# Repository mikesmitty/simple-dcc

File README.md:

# simple-dcc

A simple LCC-connected DCC command station, because sometimes a tool just needs to do the one thing.

## Features

- DCC signal generation
- RailCom cutout support
- CV writes on the main, including a long address in one step (CV17 and CV18) and advanced consists (CV19)
- CV reads on the main over RailCom, with the detector shield in `hardware/railcom-detector`
- DCC accessory decoders (turnouts and signal aspects) through the well-known LCC accessory events

## Current Reference Hardware

- **Board:** Adafruit Metro RP2350 (RP2350B, 16 MB flash)
- **Motor Shield:** EX-MotorShield8874
- **Protocol:** LCC/OpenLCB via GridConnect CAN frames over USB CDC

## Prerequisites

- [Pico SDK](https://github.com/raspberrypi/pico-sdk) (2.x)
- [FreeRTOS Kernel](https://github.com/FreeRTOS/FreeRTOS-Kernel) with RP2350 community port
- ARM GCC toolchain with newlib (e.g., [ARM GNU Toolchain](https://developer.arm.com/Tools%20and%20Software/GNU%20Toolchain))
- CMake 3.13+
- [picotool](https://github.com/raspberrypi/picotool) (for UF2 generation)

### macOS (Homebrew)

```bash
brew install cmake
brew install --cask gcc-arm-embedded
brew install picotool
```

### Clone dependencies

```bash
# Pico SDK
git clone https://github.com/raspberrypi/pico-sdk.git
cd pico-sdk && git submodule update --init && cd ..

# FreeRTOS Kernel (with RP2350 community port)
git clone https://github.com/FreeRTOS/FreeRTOS-Kernel.git
cd FreeRTOS-Kernel && git submodule update --init && cd ..
```

## Build

Set environment variables pointing to the SDK and FreeRTOS Kernel:

```bash
export PICO_SDK_PATH=/path/to/pico-sdk
export FREERTOS_KERNEL_PATH=/path/to/FreeRTOS-Kernel
```

If the ARM toolchain is not on your PATH, also set:

```bash
export PICO_TOOLCHAIN_PATH=/path/to/arm-none-eabi/bin
```

Then build:

```bash
mkdir build && cd build
cmake ..
make -j$(nproc)
```

Output: `build/simple-dcc.uf2`

## Flash

1. Hold BOOT on the Metro and connect USB
2. Drag `simple-dcc.uf2` to the mounted `RP2350` drive

Or use picotool:

```bash
picotool load build/simple-dcc.uf2
picotool reboot
```

## Host-side Tests

Unit tests run on the host (no hardware required):

```bash
cd test
mkdir -p build && cd build
cmake .. && make && ctest
```

## License

MIT

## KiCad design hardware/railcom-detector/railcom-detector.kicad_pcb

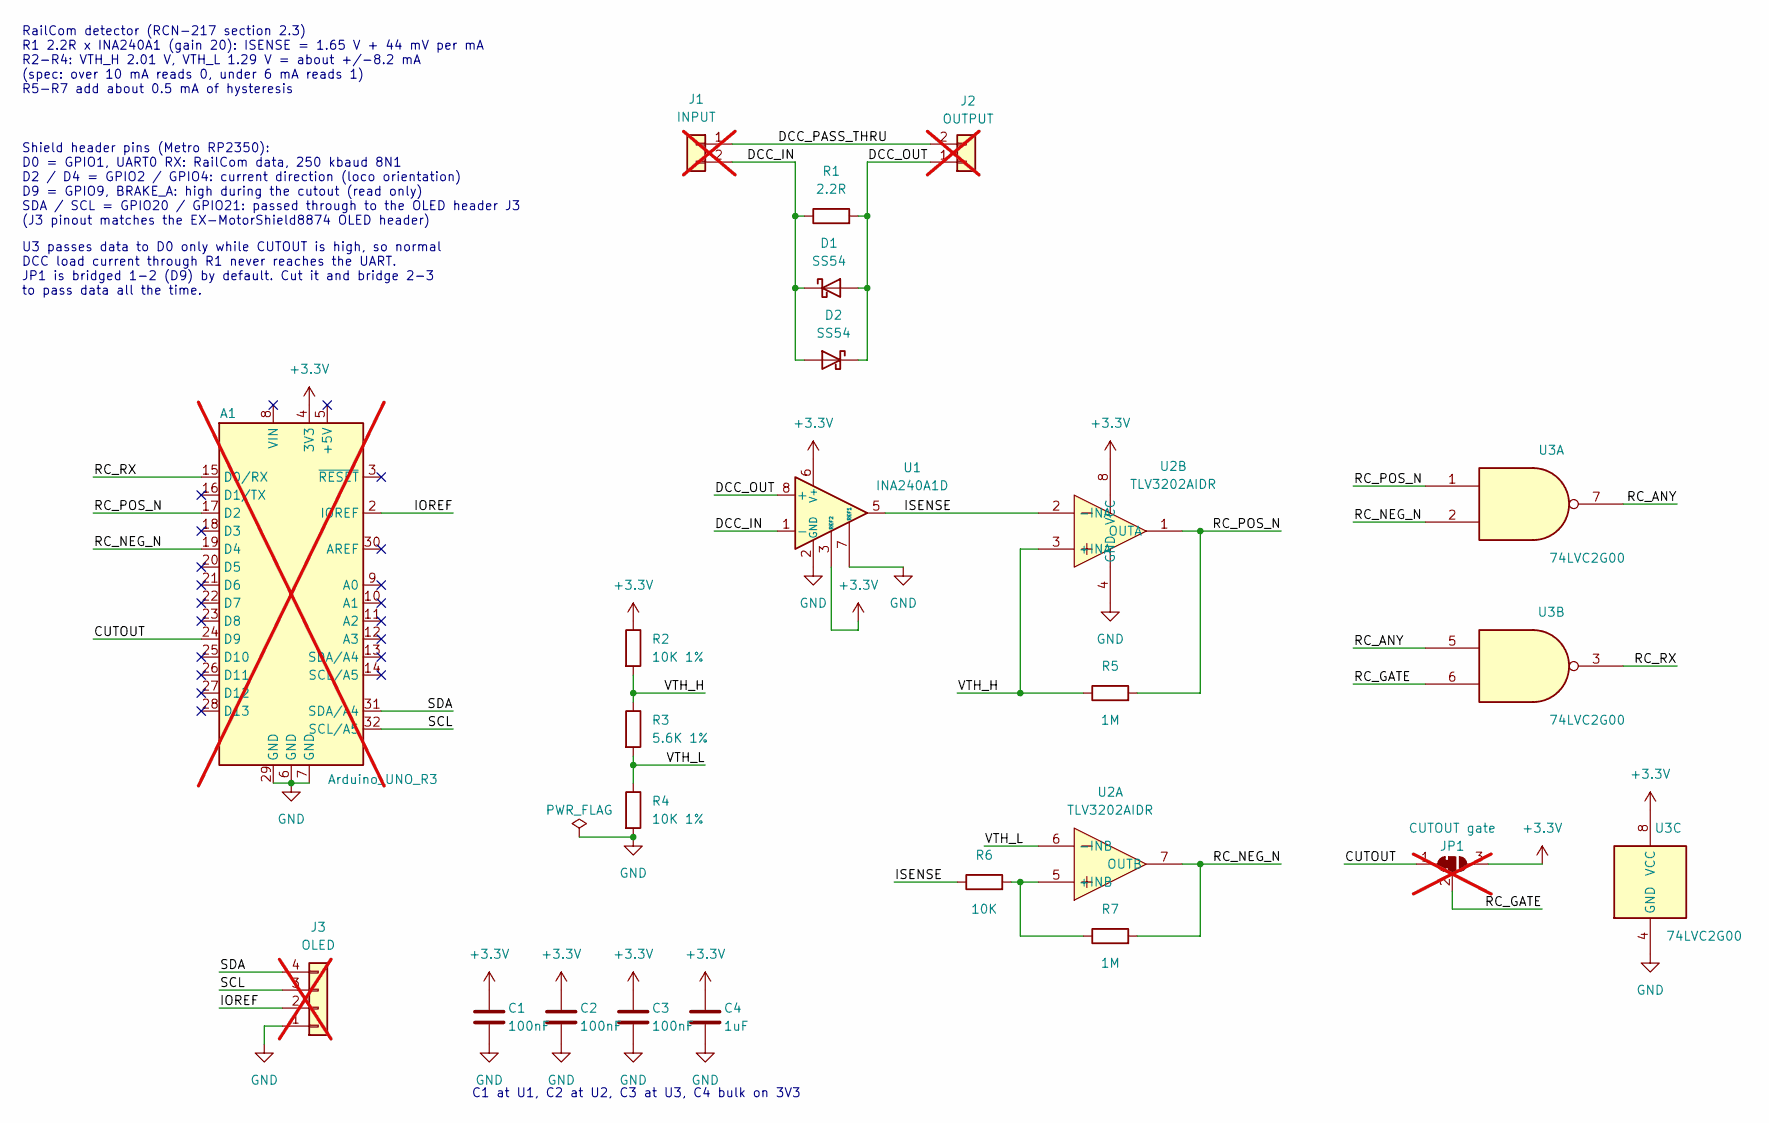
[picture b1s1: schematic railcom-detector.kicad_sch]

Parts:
A1: Arduino_UNO_R3; Arduino_UNO_R3_Shield; not fitted
C1, C2, C3: 100nF; C_0603_1608Metric; LCSC C14663
C4: 1uF; C_0603_1608Metric; LCSC C15849
D1, D2: SS54; D_SMA; LCSC C22452
J1: INPUT; PhoenixContact_MC_1,5_2-G-3.5_1x02_P3.50mm_Horizontal; LCSC C409115; not fitted
J2: OUTPUT; PhoenixContact_MC_1,5_2-G-3.5_1x02_P3.50mm_Horizontal; LCSC C409115; not fitted
J3: OLED; PinSocket_1x04_P2.54mm_Vertical; LCSC C2685089; not fitted
JP1: CUTOUT gate; SolderJumper-3_P1.3mm_Bridged12_RoundedPad1.0x1.5mm_NumberL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; not fitted
R1: 2.2R; R_2512_6332Metric; LCSC C2907574
R2, R4: 10K 1%; R_0603_1608Metric; LCSC C25804
R3: 5.6K 1%; R_0603_1608Metric; LCSC C23189
R5, R7: 1M; R_0603_1608Metric; LCSC C22935
R6: 10K; R_0603_1608Metric; LCSC C25804
U1: INA240A1D; SOIC-8_3.9x4.9mm_P1.27mm; LCSC C2060769
U2: TLV3202AIDR; SOIC-8_L4.9-W3.9-P1.27-LS6.0-BL; MPN TLV3202AIDR; LCSC Part C129325
U3: 74LVC2G00; SSOP-8_2.95x2.8mm_P0.65mm; MPN SN74LVC2G00DCTR; LCSC C2682112

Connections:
+3.3V: A1.4 (3V3), C1.1, C2.1, C3.1, C4.1, JP1.3 (B), R2.1, U1.3 (REF2), U1.6 (V+), U2.8 (VCC), U3.8 (VCC)
/CUTOUT: A1.24 (D9), JP1.1 (A)
/DCC_IN: D1.1 (K), D2.2 (A), J1.2, R1.1, U1.1 (-)
/DCC_OUT: D1.2 (A), D2.1 (K), J2.1, R1.2, U1.8 (+)
/DCC_PASS_THRU: J1.1, J2.2
/IOREF: A1.2 (IOREF), J3.2
/ISENSE: R6.1, U1.5, U2.2 (-INA)
/RC_ANY: U3.5, U3.7
/RC_GATE: JP1.2 (C), U3.6
/RC_NEG_N: A1.19 (D4), R7.2, U2.7 (OUTB), U3.2
/RC_POS_N: A1.17 (D2), R5.2, U2.1 (OUTA), U3.1
/RC_RX: A1.15 (D0/RX), U3.3
/SCL: A1.32 (SCL/A5), J3.3
/SDA: A1.31 (SDA/A4), J3.4
/VTH_H: R2.2, R3.1, R5.1, U2.3 (+INA)
/VTH_L: R3.2, R4.1, U2.6 (-INB)
GND: A1.6 (GND), A1.7 (GND), A1.29 (GND), C1.2, C2.2, C3.2, C4.2, J3.1, R4.2, U1.2 (GND), U1.4 (GND), U1.7 (REF1), U2.4 (GND), U3.4 (GND)
unnamed: R6.2, R7.1, U2.5 (+INB)

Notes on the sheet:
U3 passes data to D0 only while CUTOUT is high, so normal DCC load current through R1 never reaches the UART. JP1 is bridged 1-2 (D9) by default. Cut it and bridge 2-3 to pass data all the time.
C1 at U1, C2 at U2, C3 at U3, C4 bulk on 3V3
Shield header pins (Metro RP2350): D0 = GPIO1, UART0 RX: RailCom data, 250 kbaud 8N1 D2 / D4 = GPIO2 / GPIO4: current direction (loco orientation) D9 = GPIO9, BRAKE_A: high during the cutout (read only) SDA / SCL = GPIO20 / GPIO21: passed through to the OLED header J3 (J3 pinout matches the EX-Moto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
RailCom detector (RCN-217 section 2.3) R1 2.2R x INA240A1 (gain 20): ISENSE = 1.65 V + 44 mV per mA R2-R4: VTH_H 2.01 V, VTH_L 1.29 V = about +/-8.2 mA (spec: over 10 mA reads 0, under 6 mA reads 1) R5-R7 add about 0.5 mA of hysteresis

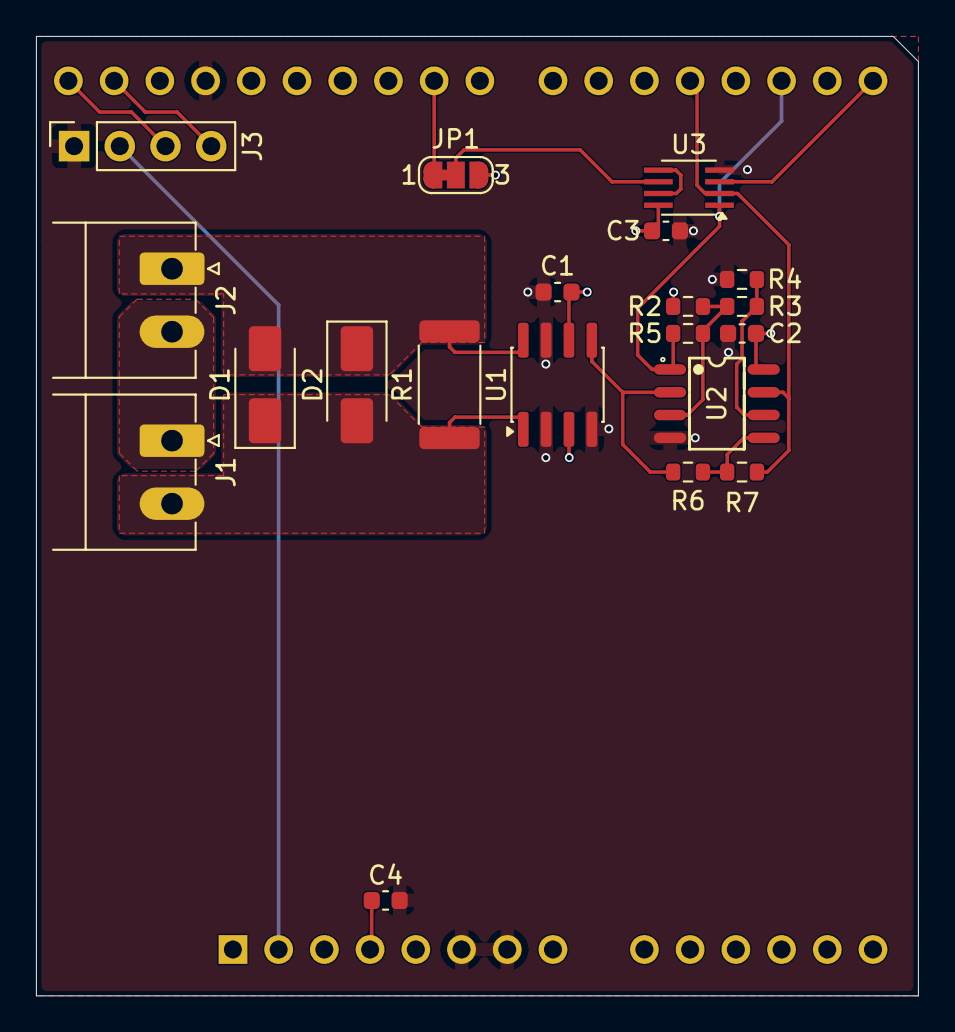
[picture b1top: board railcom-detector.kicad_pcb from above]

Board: 4 copper layers, 49.0 x 53.3 mm, 21 parts (1 on the bottom side), 18 nets.

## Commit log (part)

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2026-03-27 docs: clean up initial README
2026-03-27 chore: remove .vscode from .gitignore
2026-03-28 chore: add Makefile for ease of building
2026-03-28 feat(lcc): add CDI and RAM-backed config memory
    - Add src/cdi.xml with initial node identification and traction settings.
    - Generate src/cdi_data.c/h with pretty-printed XML (1204 bytes).
    - Fix 'premature end of file' in JMRI by excluding null terminator from reported CDI space.
    - Fix 'element type cdi must be followed by attribute' by ensuring root attributes are space-separated.
    - Implement RAM-backed config memory (space 0xFD) for CS settings like auto-claim.
    - Support auto-claim DCC address enable/disable toggle via LCC configuration.
2026-03-28 fix(lcc): save config to flash without stack overflow
    - Use heap allocation in nv_storage_write to prevent timer task stack overflow
    - Align cs_config_mem to 256 bytes for flash programming
    - Reset node run_state to RUNSTATE_INIT when releasing controllers
    - Add diagnostic logging for flash initialization and LccPro write attempts
2026-03-28 chore(main): release 0.2.0
2026-03-28 chore(main): release 0.2.0 (#2)
2026-03-28 fix: update UF2 filename in release-please workflow and docs
2026-03-28 chore(main): release 0.2.1
2026-03-28 chore(main): release 0.2.1 (#4)
2026-03-28 fix: grant contents: write permission for firmware release upload
2026-03-28 chore(main): release 0.2.2
2026-03-28 chore(main): release 0.2.2 (#5)
2026-03-28 fix: automate firmware version updates and asset uploads
2026-03-28 chore(main): release 0.2.3
2026-03-28 chore(main): release 0.2.3 (#6)
2026-03-28 fix: explicit dependency on generated cdi_data.c
2026-03-28 chore(main): release 0.2.4
2026-03-28 chore(main): release 0.2.4 (#7)
2026-03-29 feat(protocol): implement unique Proxy Node IDs and command enforcement
    - Derived unique train Node IDs from board unique ID to prevent bus collisions.
    - Implemented controller-only authorization for traction commands (speed, functions).
    - Added support for search flags (allocate, long address).
    - Refined discovery logic to respond only to this station's ID range.
2026-03-29 chore(submodule): point OpenLcbCLib to mikesmitty fork with authorization fix
2026-03-29 test(protocol): add host-side unit tests for LCC traction and interface
    - Created test_lcc_traction.c to verify speed mapping, search flags, and address logic.
    - Created test_lcc_interface.c to verify unique Node ID generation and selective discovery.
    - Added mock headers for FreeRTOS, Pico SDK, and SEGGER_RTT to enable host builds.
2026-03-29 chore(main): release 0.3.0
2026-03-29 chore(main): release 0.3.0 (#8)
2026-03-29 feat(lcc): add dynamic configuration for RailCom, current limits, and pins
    - Implemented RailCom cutout toggle via LCC CDI configuration.
    - Added configurable track current limits (mA) for Main and Prog tracks.
    - Moved motor driver GPIO pin assignments to LCC configuration memory.
    - Added configuration migration logic to populate safe hardware defaults.
    - Reorganized CDI into logical segments (Features, Limits, Pins).
    - Added comprehensive unit tests for configuration and dynamic updates.
2026-03-30 chore(main): release 0.4.0
2026-03-30 chore(main): release 0.4.0 (#9)
2026-04-15 chore(deps): add renovate.json
2026-04-19 chore: update templated pico sdk import
2026-04-21 chore(main): release 0.5.0
